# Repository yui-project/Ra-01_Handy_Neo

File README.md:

# Ra-01_Handy_Neo
## やりたいこと（適当）
- PC接続を不要にする
  - 0~9，Enter, BS, 文字切り替えの13ボタンによって、文字入力
  - キャラクターLCRによって、画面表示

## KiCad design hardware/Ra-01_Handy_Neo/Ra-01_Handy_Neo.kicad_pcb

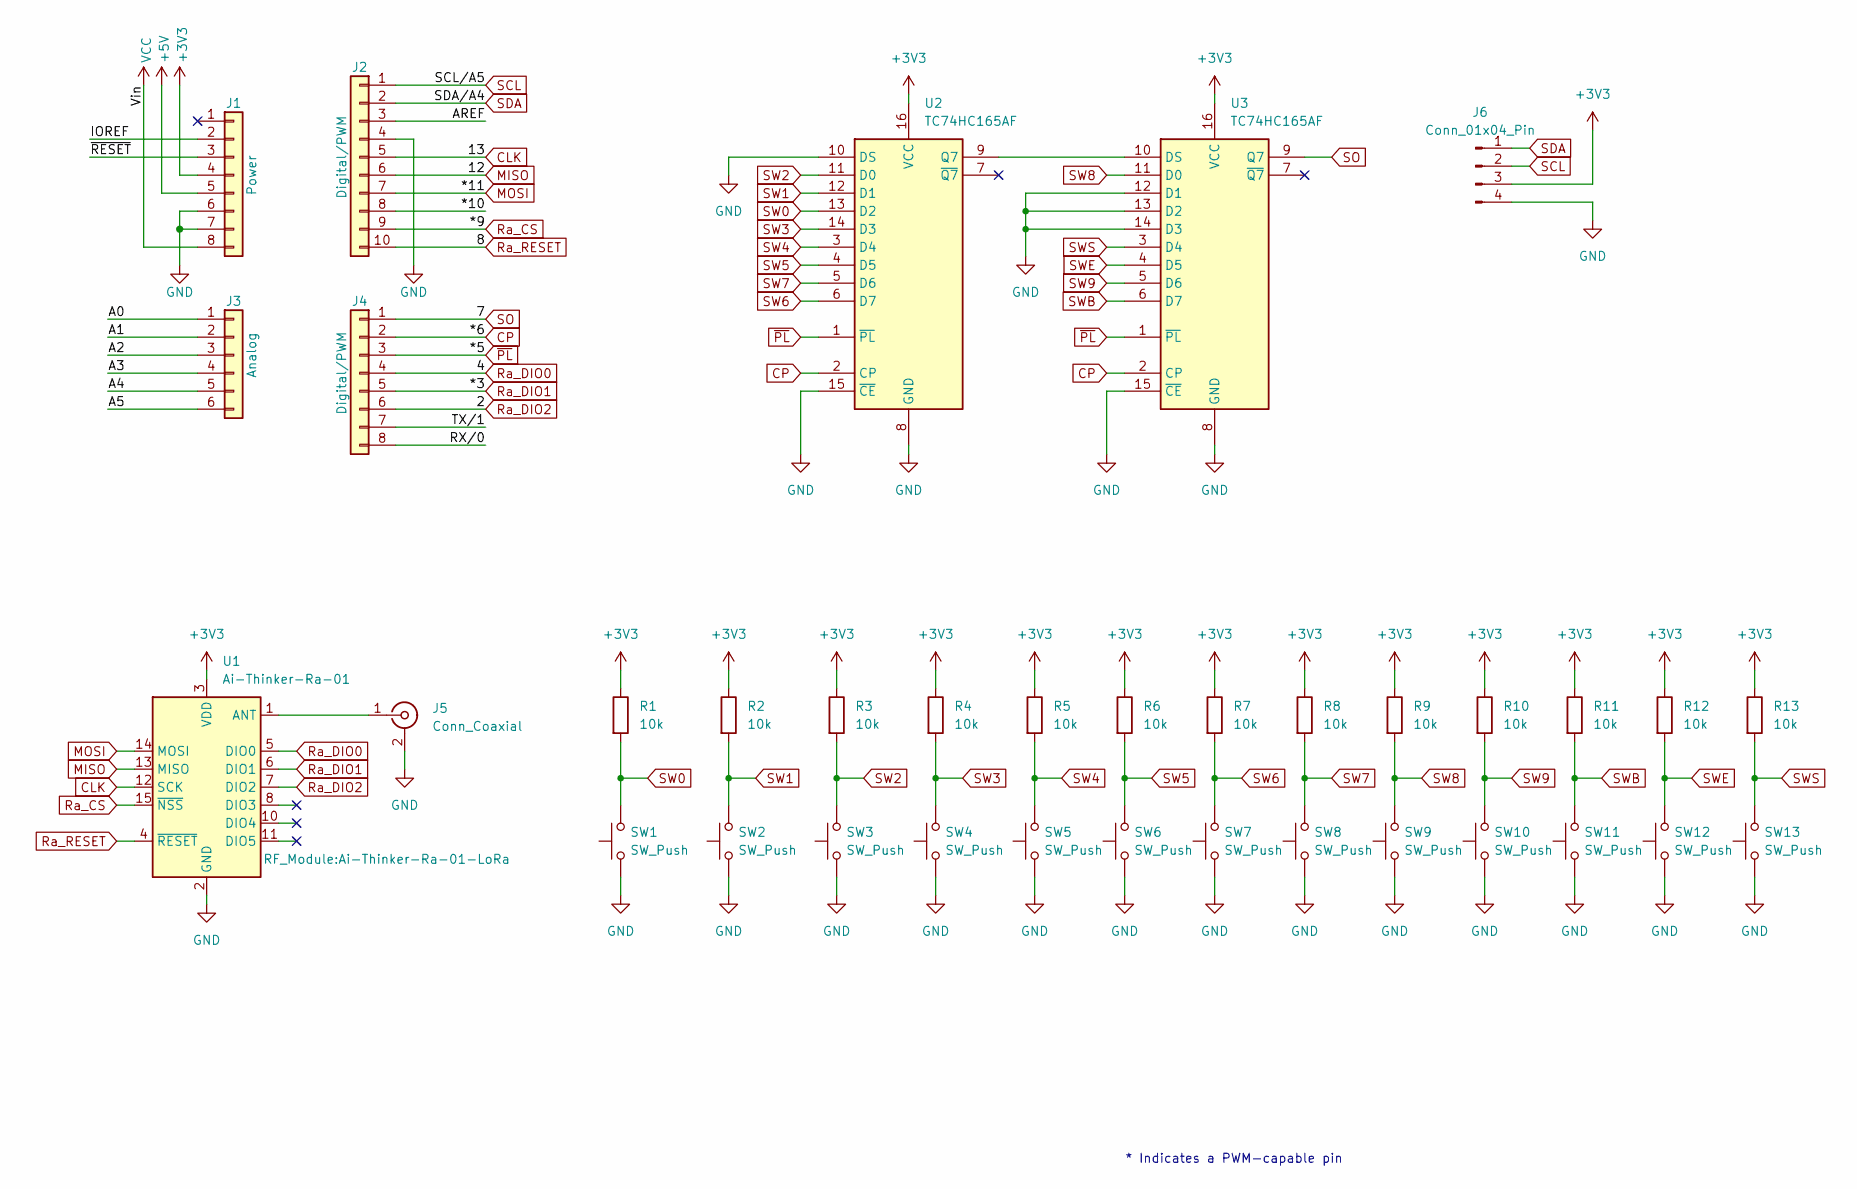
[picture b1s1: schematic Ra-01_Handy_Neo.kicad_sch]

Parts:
J1: Power; PinHeader_1x08_P2.54mm_Vertical
J2: Digital/PWM; PinHeader_1x10_P2.54mm_Vertical
J3: Analog; PinHeader_1x06_P2.54mm_Vertical
J4: Digital/PWM; PinHeader_1x08_P2.54mm_Vertical
J5: Conn_Coaxial; SMA_Connector_at_Honbu_3-1478978-1
J6: Conn_01x04_Pin; PinHeader_1x04_P2.54mm_Horizontal
R1, R2, R3, R4, R5, R6, R7, R8, R9, R10, R11, R12, R13: 10k; R_0603_1608Metric_Pad0.98x0.95mm_HandSolder
SW1, SW2, SW3, SW4, SW5, SW6, SW7, SW8, SW9, SW10, SW11, SW12, SW13: SW_Push; SW_PUSH_6mm_H6.5mm
U1: Ai-Thinker-Ra-01; Ai-Thinker-Ra-01-LoRa
U2, U3: TC74HC165AF; JEITA_SOIC-16_3.9x9.9mm_P1.27mm

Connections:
+3V3: J1.4, J6.3, R1.1, R2.1, R3.1, R4.1, R5.1, R6.1, R7.1, R8.1, R9.1, R10.1, R11.1, R12.1, R13.1, U1.3 (VDD), U2.16 (VCC), U3.16 (VCC)
+5V: J1.5
/*10: J2.8
/A0: J3.1
/A1: J3.2
/A2: J3.3
/A3: J3.4
/A4: J3.5
/A5: J3.6
/AREF: J2.3
/IOREF: J1.2
/RX/0: J4.8
/TX/1: J4.7
/~RESET: J1.3
CLK: J2.5, U1.12 (SCK)
CP: J4.2, U2.2 (CP), U3.2 (CP)
GND: J1.6, J1.7, J2.4, J5.2 (Ext), J6.4, SW1.1, SW2.1, SW3.1, SW4.1, SW5.1, SW6.1, SW7.1, SW8.1, SW9.1, SW10.1, SW11.1, SW12.1, SW13.1, U1.2 (GND), U1.9 (GND), U1.16 (GND), U2.8 (GND), U2.10 (DS), U2.15 (~CE), U3.8 (GND), U3.12 (D1), U3.13 (D2), U3.14 (D3), U3.15 (~CE)
MISO: J2.6, U1.13 (MISO)
MOSI: J2.7, U1.14 (MOSI)
unnamed: J5.1 (In), U1.1 (ANT)
unnamed: U2.9 (Q7), U3.10 (DS)
Ra_CS: J2.9, U1.15 (~NSS)
Ra_DIO0: J4.4, U1.5 (DIO0)
Ra_DIO1: J4.5, U1.6 (DIO1)
Ra_DIO2: J4.6, U1.7 (DIO2)
Ra_RESET: J2.10, U1.4 (~RESET)
SCL: J2.1, J6.2
SDA: J2.2, J6.1
SO: J4.1, U3.9 (Q7)
SW0: R1.2, SW1.2, U2.13 (D2)
SW1: R2.2, SW2.2, U2.12 (D1)
SW2: R3.2, SW3.2, U2.11 (D0)
SW3: R4.2, SW4.2, U2.14 (D3)
SW4: R5.2, SW5.2, U2.3 (D4)
SW5: R6.2, SW6.2, U2.4 (D5)
SW6: R7.2, SW7.2, U2.6 (D7)
SW7: R8.2, SW8.2, U2.5 (D6)
SW8: R9.2, SW9.2, U3.11 (D0)
SW9: R10.2, SW10.2, U3.5 (D6)
SWB: R11.2, SW11.2, U3.6 (D7)
SWE: R12.2, SW12.2, U3.4 (D5)
SWS: R13.2, SW13.2, U3.3 (D4)
VCC: J1.8
~PL: J4.3, U2.1 (~PL), U3.1 (~PL)

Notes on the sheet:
* Indicates a PWM-capable pin

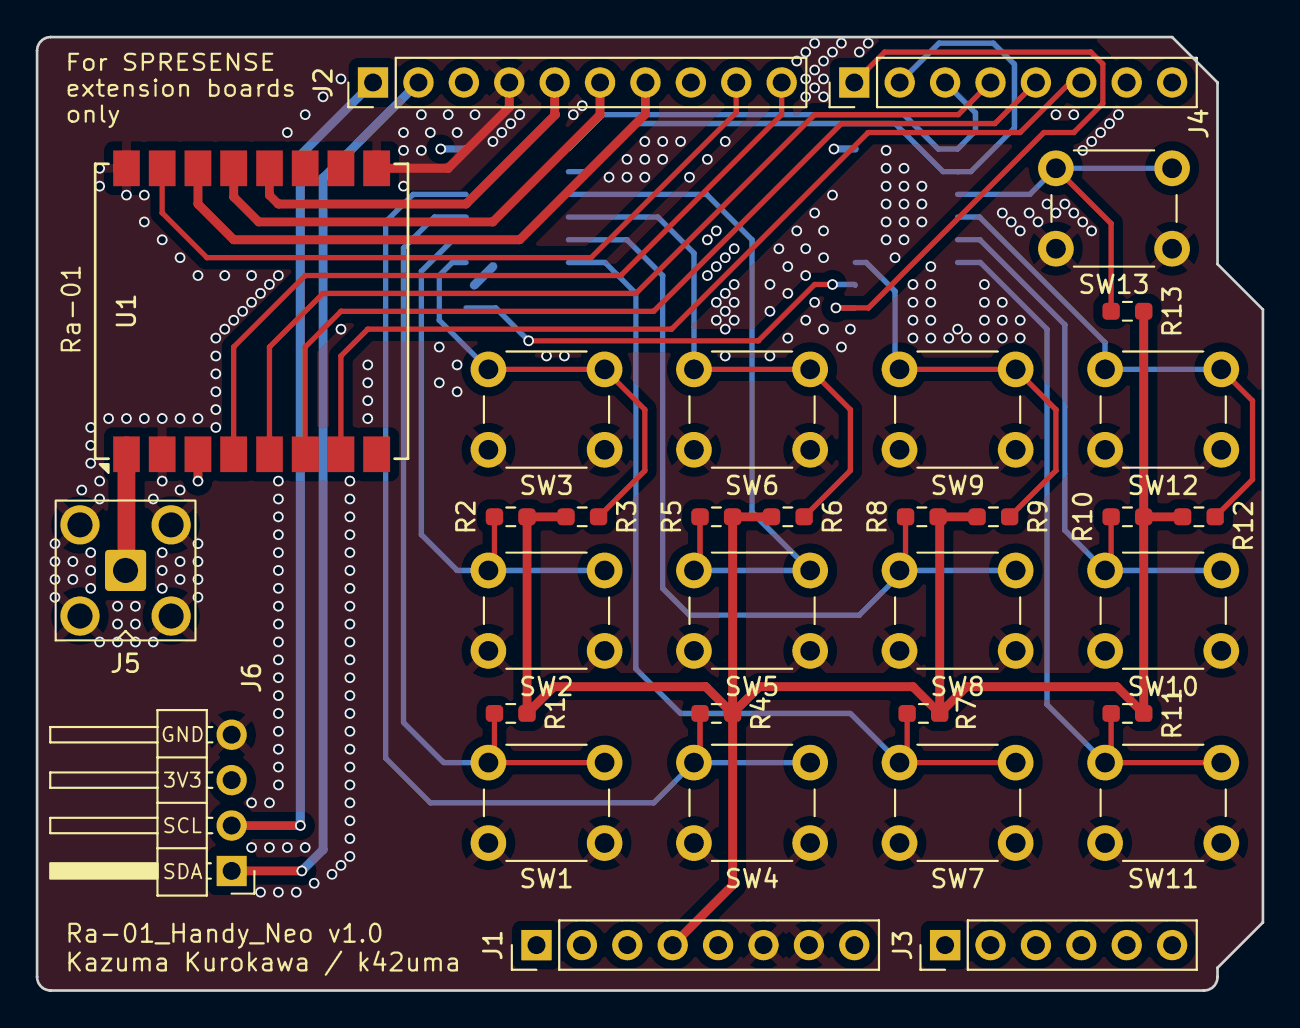
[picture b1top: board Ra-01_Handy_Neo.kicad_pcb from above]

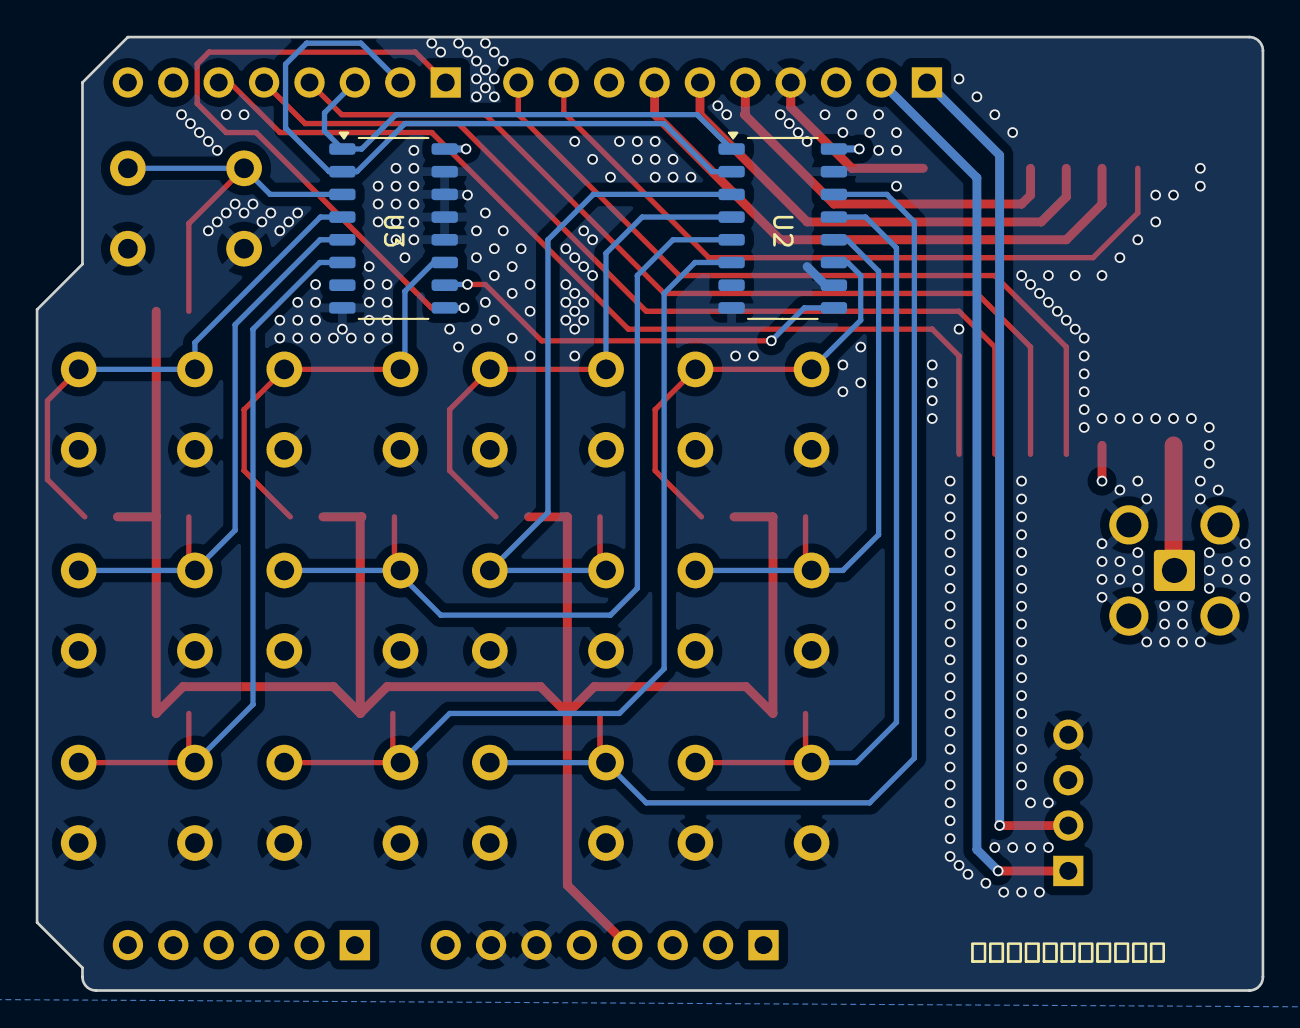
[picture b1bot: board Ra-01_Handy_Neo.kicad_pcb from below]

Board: 4 copper layers, 68.6 x 53.3 mm, 35 parts (2 on the bottom side), 30 nets.

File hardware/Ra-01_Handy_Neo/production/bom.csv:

Designator,Footprint,Quantity,Value,LCSC Part #
J1,PinHeader_1x08_P2.54mm_Vertical,1,Power,
J2,PinHeader_1x10_P2.54mm_Vertical,1,Digital/PWM,
J3,PinHeader_1x06_P2.54mm_Vertical,1,Analog,
J4,PinHeader_1x08_P2.54mm_Vertical,1,Digital/PWM,
J5,SMA_BAT_Wireless_BWSMA-KWE-Z001,1,Conn_Coaxial,
J6,PinHeader_1x04_P2.54mm_Horizontal,1,Conn_01x04_Pin,
"R1, R10, R11, R12, R13, R2, R3, R4, R5, R6, R7, R8, R9",0603,13,10k,
"SW1, SW10, SW11, SW12, SW13, SW2, SW3, SW4, SW5, SW6, SW7, SW8, SW9",SW_PUSH_6mm_H5mm,13,SW_Push,
U1,Ai-Thinker-Ra-01-LoRa,1,Ai-Thinker-Ra-01,
"U2, U3",JEITA_SOIC-16_3.9x9.9mm_P1.27mm,2,TC74HC165AF,

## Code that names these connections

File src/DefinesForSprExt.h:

// Situation Defines
// #define BUTTON_TEST // ボタン類のテスト
// #define ENTER_TEST // 文字入力テスト
// #define DISPLAY_TEST // ディスプレイ表示テスト // 非推奨
// #define YUI_LOGO_TEST // 起動時に結ロゴを表示するテスト
#define DEFAULT // 通常使用時

#define IS_SERIAL // 【すべてのコンポーネントで】シリアル通信でのデバッグ出力を有効にする

// params
#define OPENING_YUI_LOGO // 起動時に結ロゴを表示する

#define LOG_CAPACITY 128
#define LOG_DATA_MAX_LEN 64

#define SD_CARD_SEARCHING_COUNT 6

// Digital Pins
#define RA_CS 9
#define RA_RESET 10
#define RA_DIO0 4
#define RA_DIO1 3
#define RA_DIO2 2

#define BSR_SO 7
#define BSR_CP 6
#define BSR_PL 5

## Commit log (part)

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2026-05-08 add todo to README
2026-05-08 add templates
2026-05-09 add feature to README
2026-05-09 add buttons and ra01 to sch
2026-05-11 80% done
2026-05-11 koshin
2026-05-12 pcb almost complete
2026-05-12 add gitignore to ignore kicad backups
2026-05-12 modify back silkscreen
2026-05-13 change designs
2026-05-13 write codes jal
2026-05-14 change Resister posi
2026-05-14 add keying sys to src
2026-05-14 del old dir
2026-05-14 add ssd1306 example
2026-05-14 hardware: push files for jlcpcb
2026-05-15 change footprints and 3dsymbols to export step file
2026-05-15 update src for alphabet mode
2026-05-15 do operation donfirmation asap
2026-05-16 alphabet mode added
2026-05-16 add \0
2026-05-16 add ra01 file
2026-05-16 comment out while loop
2026-05-17 RIP denshi kairo
2026-05-17 where is denshi kairo
2026-05-18 add send tests
2026-05-19 kekkou dekita
2026-05-20 add log system
2026-05-21 add log save to sd sys
2026-05-21 add correct showRecv before ope conf
2026-05-21 after clauding
2026-05-21 add gnss test
2026-05-23 almost complete, and after this i gonna use sub branches
2026-05-23 transplant gnss.ino to src.ino(mainfile)
2026-05-23 kanse
